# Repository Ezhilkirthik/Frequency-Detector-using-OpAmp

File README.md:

# Frequency Detection Circuit Using Op-Amps

## Overview

This project involves the design, simulation, and implementation of a frequency detection circuit using operational amplifiers. The circuit converts an unknown sinusoidal input signal into a DC voltage proportional to its frequency. The project includes schematic and PCB design files, simulation results, and a detailed technical report.

---

## 📌 Objective

To create a circuit capable of detecting the frequency of a sinusoidal signal and converting it into a measurable DC voltage, enabling frequency analysis without an oscilloscope or frequency counter.

---

## 🧠 Working Principle

1. **Signal Conditioning**: The sinusoidal input is first conditioned using an op-amp-based zero-crossing detector to generate a square wave.
2. **Monostable Multivibrator**: Converts each cycle into a pulse of fixed duration.
3. **Integrator or Low-Pass Filter**: Averages the pulse train into a DC voltage that varies linearly with frequency.
4. **Output Stage**: The final DC output can be read using a multimeter.

---

## 🔧 Tools and Technologies Used

- **LTspice**: For simulating and validating the circuit behavior.
- **EAGLE**: For schematic design and PCB layout.
- **Op-Amps**: Used for signal processing stages (e.g., LM324 or equivalent).
- **Multimeter**: To measure the output DC voltage corresponding to frequency.

---

## 🗂️ Project Files

| File | Description |
|------|-------------|
| `PCB design.brd` | EAGLE board layout file |
| `PCB design.sch` | EAGLE schematic file |
| `PCB design.png` | Schematic/PCB image preview |
| `README.md` | Project documentation |
| `Report on Frequency Detector.pdf` | Detailed explanation of theory, design, calculations, and results |
| `design blocks.dbl` | Block diagram or design structure file (assumed for visual layout or planning) |
| `*.asc` / LTspice files | Simulation circuits and results |

---

## ✅ Features

- Converts sinusoidal signals (variable frequency) to a DC voltage output.
- Linear relationship between frequency and voltage.
- Suitable for real-time monitoring with minimal hardware.
- Compact and low-cost solution.

---

## 📈 Simulation and Testing

- Simulated using LTspice to validate performance and linearity.
- Output voltage was tested across a range of frequencies to confirm consistency.
- PCB designed and reviewed for real-world implementation.

---

## 🧪 Applications

- Educational demonstration of frequency detection.
- Basic instrumentation projects.
- Embedded systems requiring analog frequency monitoring.
- Low-cost signal analysis setups.

---

## 📎 How to Use

1. Connect the sinusoidal input signal to the input terminal of the circuit.
2. Power the op-amp circuit with the recommended dual or single power supply.
3. Read the output voltage using a multimeter.
4. Use the linear transfer function (from report) to interpret the frequency.

---

## 📃 Documentation

Please refer to `Report on Frequency Detector.pdf` for:

- Complete theoretical background
- Circuit analysis and calculations
- Design decisions
- PCB snapshots
- Testing and result interpretation

---

## 📌 Notes

- Ensure proper power supply filtering for accurate readings.
- Input signal should be within expected amplitude range for reliable zero-crossing detection.
- Calibration may be required depending on the op-amp and resistor tolerances used.

---

## 🛠️ Future Improvements

- Add microcontroller interface to digitally display the frequency.
- Expand range using frequency dividers or advanced signal conditioning.
- Implement auto-scaling for broader frequency bands.

---

## 👨‍💻 Author

*Ezhilkirthik M*  
*AMRITA SCHOOL OF ENGINEERING, AMRITA VISHWA VIDYAPEETHAM *  
*Date: 01 April 2025*

---

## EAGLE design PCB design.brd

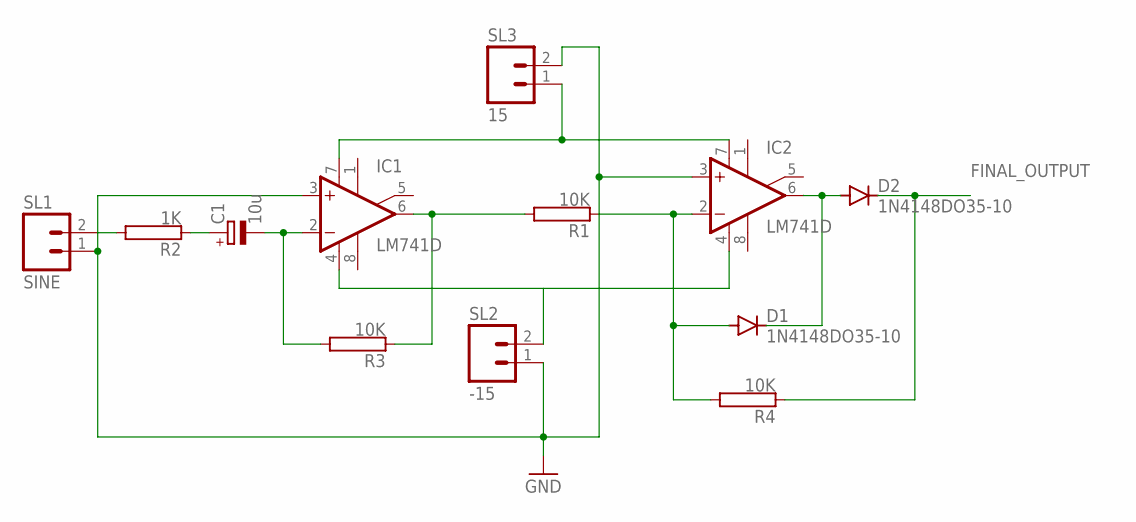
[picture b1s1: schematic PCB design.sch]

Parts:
C1: 10u; E2,5-5
D1, D2: 1N4148DO35-10; DO35-10
IC1, IC2: LM741D; SO08
R1, R3, R4: 10K; TO-247-2V
R2: 1K; TO-247-2V
SL1: SINE; 02P
SL2: -15; 02P
SL3: 15; 02P

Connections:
FINAL_OUTPUT: D2.C, R4.1
GND: IC1.3 (+IN), IC2.3 (+IN), SL1.1, SL2.1, SL3.2
unnamed: C1.+, R2.1
unnamed: IC1.6 (OUT), R1.2, R3.1
unnamed: D1.A, IC2.2 (-IN), R1.1, R4.2
unnamed: D1.C, D2.A, IC2.6 (OUT)
unnamed: IC1.7 (V+), IC2.7 (V+), SL3.1
unnamed: IC1.4 (V-), IC2.4 (V-), SL2.2
unnamed: R2.2, SL1.2
unnamed: C1.-, IC1.2 (-IN), R3.2

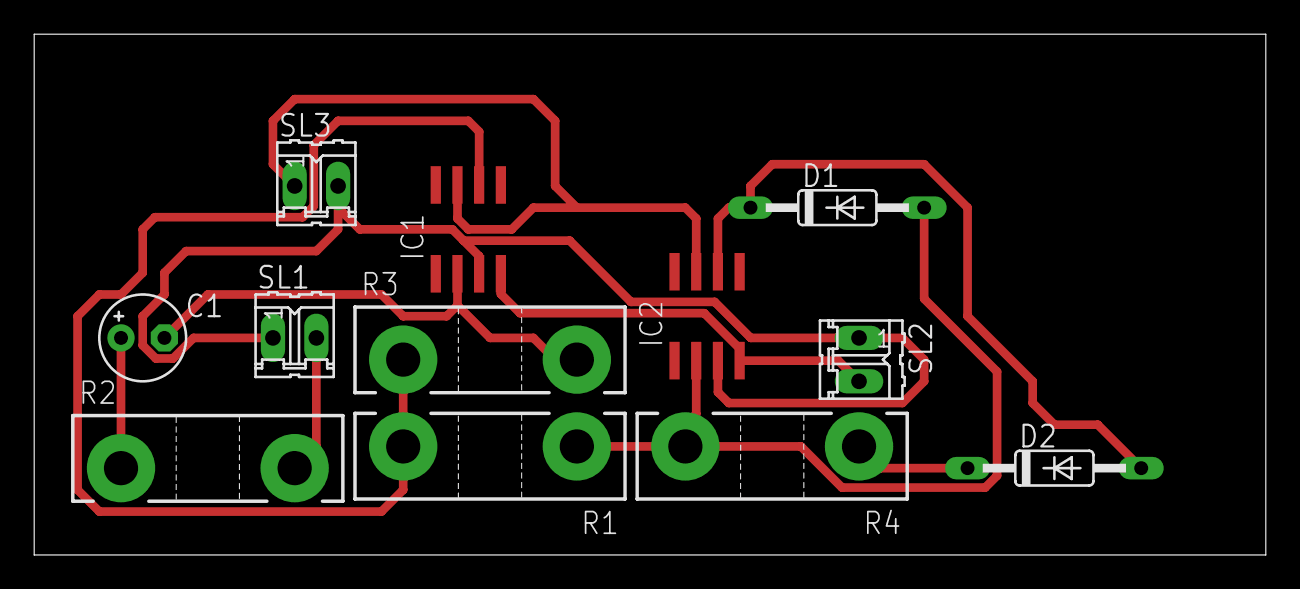
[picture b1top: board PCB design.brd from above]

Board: 2 copper layers, 72.1 x 30.5 mm, 12 parts (0 on the bottom side), 10 nets.
